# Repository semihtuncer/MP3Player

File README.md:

<div align='center'>

<h1>An MP3 Player I Made Using ESP32 and Custom PCB's.</h1>
<p>Since I was bothered by the heavy phone in my pocket when going to the gym, I made myself a lighter and faster MP3 player. The PCB is a shield for ESP32-WEMOS-D1-MINI, that fits perfectly to the ESP. There is no need for another phone, device works by itself. There is a SD card slot. External battery managment module (TP4056 w/ LiPo) needs to be connected.</p>

</div>

### :dart: Features
- SD card slot to store your taste in music.
- Several buttons to control the device.
- Bluetooth 4.2 connection to your favorite headphones.
- Battery management module for fast type-c charging nd 4 hours of streaming.
  
# :notebook_with_decorative_cover: Table of Contents

- [About the Project](#star2-about-the-project)

## :star2: About the Project

### :camera: Screenshots
<div align="center">  </div>
<div align="center">  </div>
<div align="center">  </div>

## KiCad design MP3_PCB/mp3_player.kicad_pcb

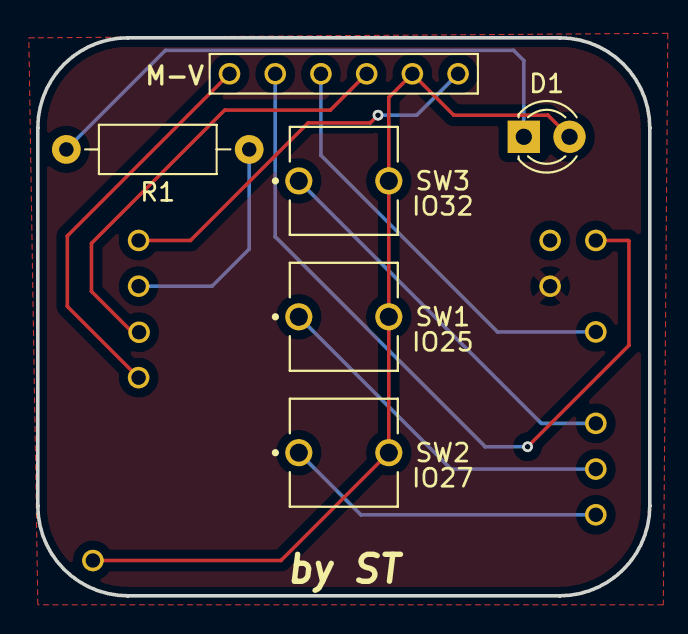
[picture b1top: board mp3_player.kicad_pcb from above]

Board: 2 copper layers, 34.0 x 31.0 mm, 7 parts (0 on the bottom side), 11 nets.

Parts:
D1: LED; LED_D3.0mm
R1: 220; R_Axial_DIN0207_L6.3mm_D2.5mm_P10.16mm_Horizontal
SW1: IO25; SW_BUTT-2
SW2: IO27; SW_BUTT-2
SW3: IO32; SW_BUTT-2
U1: through_hole_01x06_2.54mm
U3: wemos_d1_mini

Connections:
unnamed: D1.2 (A), SW1.2, SW2.2, SW3.2, U1.5 (GND), U3.11 (GND)
unnamed: D1.1 (K), R1.2
unnamed: U1.1 (MISO), U3.3 (IO19)
unnamed: U1.4 (MOSI), U3.2 (IO23)
unnamed: U1.2 (SCK), U3.4 (IO2)
unnamed: U1.3 (SS), U3.5 (IO4)
unnamed: U1.6 (Vcc), U3.9 (3.3V)
unnamed: R1.1, U3.1 (IO5)
unnamed: SW1.1, U3.6 (IO25)
unnamed: SW2.1, U3.7 (IO27)
unnamed: SW3.1, U3.8 (IO32)

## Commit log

2025-08-26 Added 3D models
